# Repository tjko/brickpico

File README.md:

# Brickpico: Smart PWM LED Controller

Bricpico is a smart PWM LED controller based around [Raspberry Pi Pico](https://www.raspberrypi.com/documentation/microcontrollers/raspberry-pi-pico.html) (RP2040 MCU).
Brickpico is mainly meant to controlling various LED lights on LEGO models, but can be used to control any LED lights (or other small loads).

Brickpico operates as standalone controller that incorporates programmable timer to turn lights on/off on a schedule.
BrickPico is an Open-source hardware (OSHW) project.

## Features
* Controls up to 8 to 16 separete channels (LED group)
* Adjustable output brightness (via PWM)
* Adjustable output voltage 5V or 3.3V
* Up to 200mA current output per port (each port has resettable fuse).
* Programmable PWM frequency from 10 to 100000 Hz
* Configurable Lightness/Gamma correction
* Support for configurable lighting "effects" on each channel
* Connectors for common Lego light kits (Light My Bricks, etc.) as well as 2.54mm pin header.
* I2C OLED display module support (128x64 or 128x128)
* I2C Enviromental sensor support (up to 8 sensors)
* Configuration stored on the device itself (in the flash memory).
* SCPI "like" programming interface (see [Command Reference](commands.md))
* WiFi support if opting to mount Pico W on the board.
* HTTP server for monitoring.
* MQTT support for sending status and to receive commands.
* Home Assistant (MQTT Discovery) support
* Telnet server for remote configuration and monitoring.
* SSH server for remote configuration and monitoring.

### Interfaces

* Serial "Console". Primary method for configuring/monitoring FanPico units is via (USB) Serial console (some units also have 3.3V TTL Serial connection).
* Telnet server allows configuration and monitoring over network.
* Web Interface (available when using _Pico W_) over WiFi

For more documentation check [BrickPico Wiki](https://github.com/tjko/brickpico/wiki)

## Where can I get one?
Initially BrickPico is only available as a DIY kit. For places to buy kits, check discussions: [Where to Buy BrickPico](https://github.com/tjko/brickpico/discussions/5)

(Instructions for building the kit can be found at: [BrickPico Wiki](https://github.com/tjko/brickpico/wiki)

### DIY Option
You can upload the Kerber files (found under boards directory) to your favorite PCB maker website and get your boards produced in matter of days.
Component list (BOM or bill of materials) is found under boards directory as well along with the electrical schematics.

### Review Units
If you are member of press (or YouTuber) and would like to review/test Brickpico. Please contact me via email.

## How Can I help?
* Build your own BrickPico and provide feedback, suggestions (see discussion forums).
* If you're into electronics new/improved board designs are most welcome.
* If you're into programming:
  - Create cool (desktop) program that allows easily configuring/controlling BrickPico boards.
  - Help improve the firmware.
* If you're into graphics (or web) design:
  - Help create cool (but lightweight) web interface
  - Create better logo for BrickPico
* As this is Open (Source) Hardware Project, if you like to build (and sell) assembled boards or DIY kits, you'd be most welcome...
* You can always donate (and get your name added to the Sponsors section, if you so wish).

## Hardware
BrickPico is Open Source Hardware, reference design is provided for the "08" model (8 outputs) and "16" model (16 outputs).

Additional models with different combinations of fan outputs could be easily designed (takining into account limitations of Raspberry Pi Pico I/O limits). New and improved PCB models/designs are most welcome.

BrickPico is loosely based on FanPico:
* [FanPico](https://github.com/tjko/fanpico/) - Open Source Smart PWM (PC) Fan Controller.

### Models (PCB designs)
Currently following models are available:

|Model|Outputs|Notes|
|-----|-------|-----|
|[BRICKPICO-08](boards/brickpico-8/)|8||
|[BRICKPICO-16](boards/brickpico-16/)|16|PCB under development|

## Firmware
Firmware is developed in C using the Pico SDK. Pre-compiled firmware is released when there is new major features or bug fixes.

Latest pre-compiled firmware image can be found here: [Releases](https://github.com/tjko/brickpico/releases)

To get latest firmware with latest updates/fixes you must compile the firmware from the sources.

### Installing firmware image
Firmware can be installed via the built-in UF2 bootloader on the Raspberry Pi Pico or using the debug header with Picoprobe, etc...

#### Selecting Right Firmware to use
Each release (zip file) contains multiple different firmware files.
Make sure to select firmware for the board you're using and for the pico model ("pico_w" if using Pico W).

Firmware file names have format: brickpico-<board_model>-<pico_model>.uf2
```
brickpico-08-pico.uf2
brickpico-08-pico_w.uf2
brickpico-16-pico.uf2
brickpico-16-pico_w.uf2
```

#### Upgrading Firmware
Firmware upgrade steps:
* Boot Pico into UF2 bootloader. This can be done in two ways:
  1)  Press and hold "bootsel" button and then press and release "reset" button.
  2)  Issue command: SYS:UPGRADE
* Copy firmware file to the USB mass storage device that appears.
* As soon as firmware copy is complete, Pico will reboot and run the fanpico firmware.

### Building Firmware Images

Raspberry Pi Pico C/C++ SDK is required for compiling the firmware:

#### Requirements / Dependencies
* [Raspberry Pi Pico C/C++ SDK](https://www.raspberrypi.com/documentation/microcontrollers/c_sdk.html)
* [cJSON](https://github.com/DaveGamble/cJSON)
* [pico-lfs](https://github.com/tjko/pico-lfs)
* [ss_oled-lib](https://github.com/tjko/ss_oled-lib)
* [libb64](https://github.com/libb64/libb64)
* [pico-telnetd](https://github.com/tjko/pico-telnetd)

##### Install Pico SDK
Pico SDK must be installed working before you can compile fanpico.

Instructions on installing Pico SDK see: [Getting started with Raspberry Pi Pico](https://datasheets.raspberrypi.com/pico/getting-started-with-pico.pdf)

(Make sure PICO_SDK_PATH environment variable is set)

##### Downloading sources

Create some directory for building fanpico ('src' used in this example):
```
$ mkdir src
$ cd src
$ git clone https://github.com/tjko/brickpico.git
$ git submodule update --init --recursive
```

##### Building fanpico firmware

To build brickpico firmware, first create a build directory:
```
$ cd brickpico
$ mkdir build
```

Select which board to build firmware for (default is "08") and which Pico is to be used (default is "pico_w"):
```
$ cd build
$ cmake -DBRICKPICO_BOARD=16 -DPICO_BOARD=pico_w ..
```

Then compile fanpico:
```
$ make -j
```

After successful compile you should see firmware binary in the build directory:
subdirectory:

```
$ ls *.uf2
brickpico.uf2
```

If you have picotool installed you can check the firmware image information:
```
$ picotool info -a brickpico.uf2
File brickpico.uf2 family ID 'rp2040':

Program Information
 name:              brickpico
 version:           1.4.0beta
 web site:          https://github.com/tjko/brickpico/
 description:       BrickPico-08 - Smart LED Controller
 features:          USB stdin / stdout
 boot settings:     bootdelay = 0
                    safemode = 0
 binary start:      0x10000000
 binary end:        0x1010b638
 embedded drive:    0x101c0000-0x10200000 (256K): littlefs

Fixed Pin Information
 0:                 TX (Serial)
 1:                 RX (Serial)
 2:                 SCK (SPI)
 3:                 MOSI (SPI)
 4:                 MISO (SPI)
 5:                 CS (SPI)
 6:                 PWM7 signal (output)
 7:                 PWM8 signal (output)
 16:                PWM1 signal (output)
 17:                PWM2 signal (output)
 18:                PWM3 signal (output)
 19:                PWM4 signal (output)
 20:                PWM5 signal (output)
 21:                PWM6 signal (output)
 22:                LCD DC (SPI)
 26:                SDA (I2C)
 27:                SCL (I2C)
 28:                LCD Reset (SPI)

Build Information
 sdk version:       2.1.1
 pico_board:        pico_w
 boot2_name:        boot2_w25q080
 build date:        Jul 14 2025
 build attributes:  Release

Metadata Blocks
 none
```

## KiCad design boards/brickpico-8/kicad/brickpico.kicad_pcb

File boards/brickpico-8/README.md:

# BRICKPICO-08 PCB

PCB Size: 86mm x 79.5mm

## Change Log

v1.0 
- First Prototye

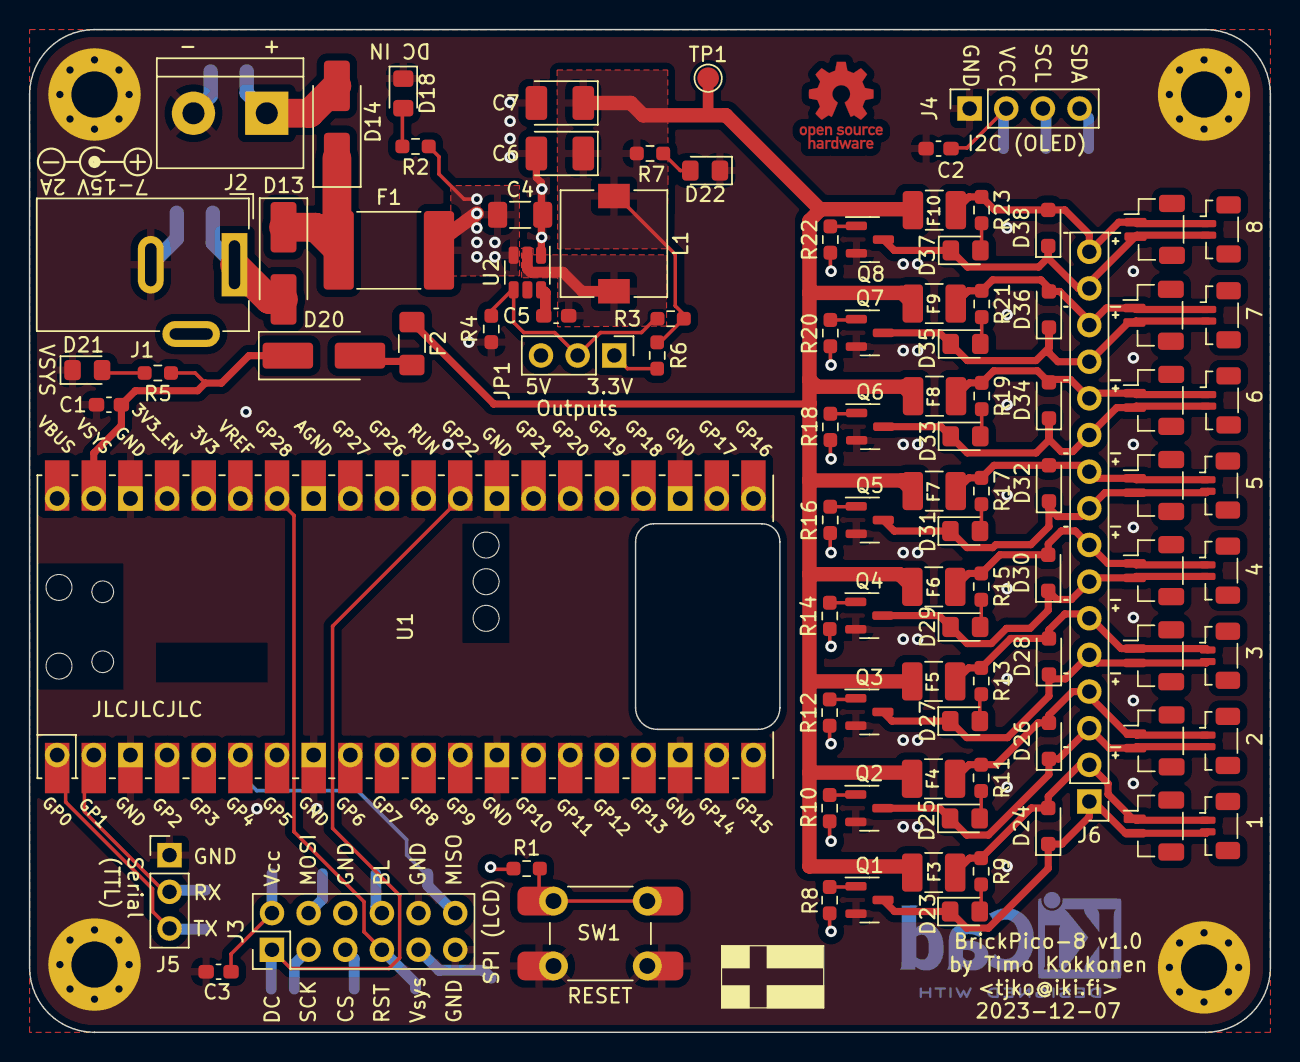
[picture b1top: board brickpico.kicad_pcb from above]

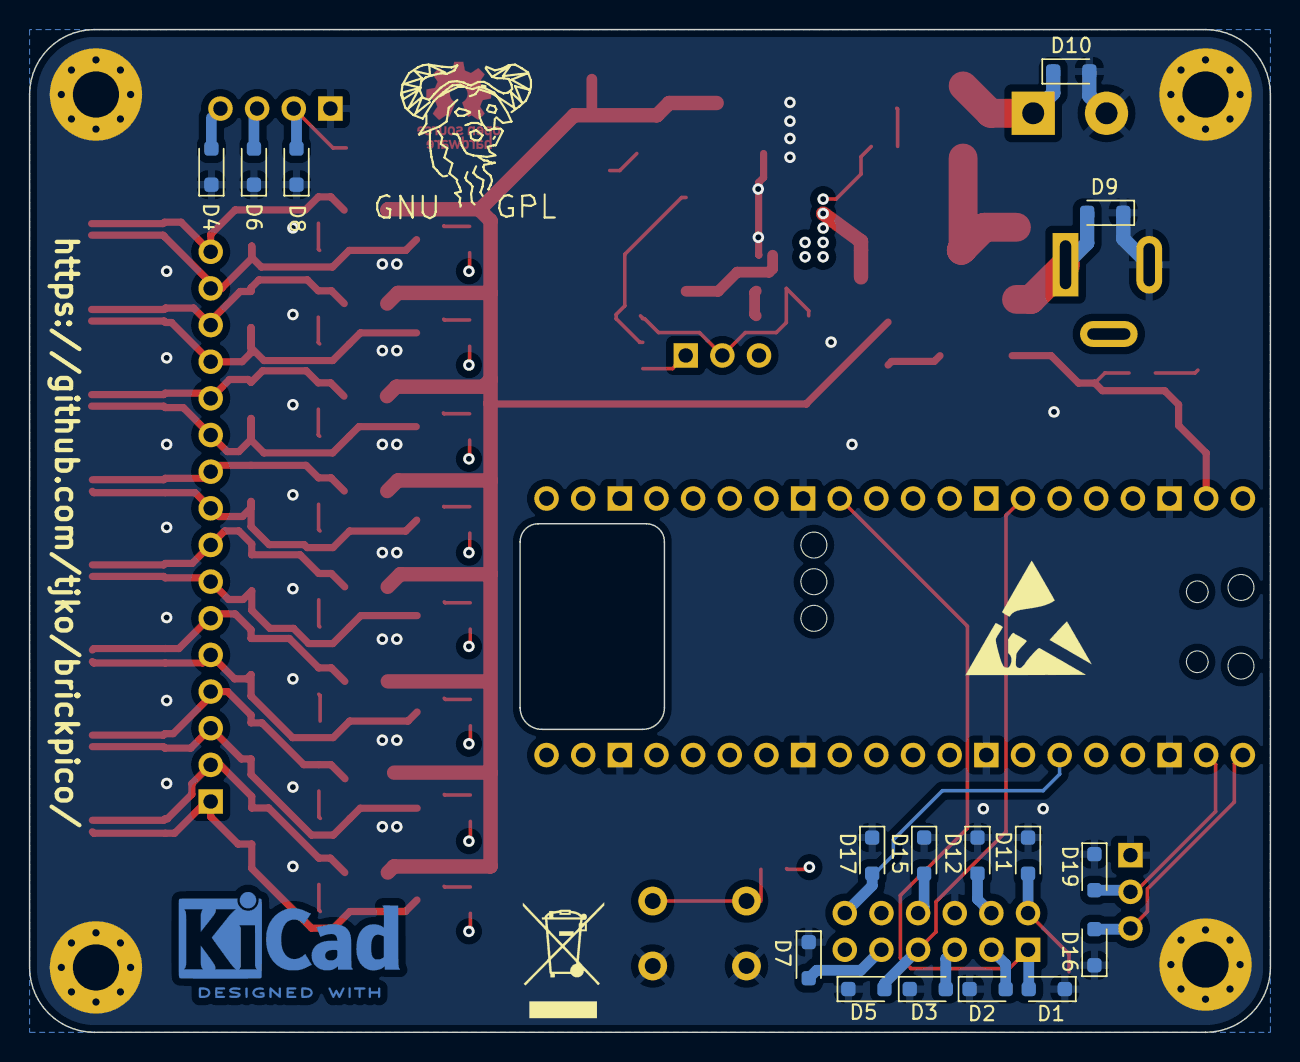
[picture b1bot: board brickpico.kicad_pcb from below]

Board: 4 copper layers, 86.0 x 69.5 mm, 118 parts (16 on the bottom side), 68 nets.

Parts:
C1, C2, C3, C5: 0.1uF; C_0603_1608Metric_Pad1.08x0.95mm_HandSolder
C4: 10uF 50V; C_1206_3216Metric_Pad1.33x1.80mm_HandSolder
C6, C7: 22uF 16V; CP_EIA-3528-21_Kemet-B_Pad1.50x2.35mm_HandSolder
D1, D2, D3, D4, D5, D6, D8, D11, D12, D15, D16, D17, D19: 3.3V; D_SOD-323_HandSoldering
D7, D24, D26, D28, D30, D32, D34, D36, D38: 5V; D_SOD-323_HandSoldering
D9, D10: 12V; D_SOD-323_HandSoldering
D13, D14: SK54A-LTP; D_SMA_Handsoldering
D18, D21, D22, D23, D25, D27, D29, D31, D33, D35, D37: LED; LED_0805_2012Metric_Pad1.15x1.40mm_HandSolder
D20: SM5819PL 1A; D_SMA_Handsoldering
F1: Polyfuse 3A; Fuse_2920_7451Metric_Pad2.10x5.45mm_HandSolder
F2: Polyfuse 500mA; Fuse_1206_3216Metric_Pad1.42x1.75mm_HandSolder
F3, F4, F5, F6, F7, F8, F9, F10: Polyfuse 200mA; Fuse_1210_3225Metric_Pad1.42x2.65mm_HandSolder
H1, H2, H3, H4: MountingHole_Pad; MountingHole_3.2mm_M3_Pad_Via
J1: DC Connector; BarrelJack_Wuerth_6941xx301002
J2: Terminal Block; TerminalBlock_bornier-2_P5.08mm
J3: SPI (LCD); PinHeader_2x06_P2.54mm_Vertical
J4: I2C (OLED); PinSocket_1x04_P2.54mm_Vertical
J5: Serial (TTL); PinHeader_1x03_P2.54mm_Vertical
J6: Conn_01x16; PinHeader_1x16_P2.54mm_Vertical
J7, J8, J9, J10, J11, J12, J13, J14: JST SUR; JST_SUR_BM02B-SURS-TF_1x02-1MP_P0.80mm_Vertical
J15, J16, J17, J18, J19, J20, J21, J22: JST SRS; JST_SH_BM02B-SRSS-TB_1x02-1MP_P1.00mm_Vertical
JP1: Conn_01x03; PinHeader_1x03_P2.54mm_Vertical
L1: 3.3uH; L_7.3x7.3_H3.5_HandSolder
Q1, Q2, Q3, Q4, Q5, Q6, Q7, Q8: 2N7002K; SOT-23
R1, R8, R10, R12, R14, R16, R18, R20, R22: 1K; R_0603_1608Metric_Pad0.98x0.95mm_HandSolder
R2: 49.9K; R_0603_1608Metric_Pad0.98x0.95mm_HandSolder
R3: 56.2K; R_0603_1608Metric_Pad0.98x0.95mm_HandSolder
R4, R5, R7, R9, R11, R13, R15, R17, R19, R21, R23: 10K; R_0603_1608Metric_Pad0.98x0.95mm_HandSolder
R6: 82K; R_0603_1608Metric_Pad0.98x0.95mm_HandSolder
SW1: Reset; SW_PUSH_6mm_SMD_2
TP1: TestPoint; TestPoint_Pad_D1.5mm
U1: Pico; RPi_Pico_PicoW_SMD_TH
U2: AP62300TWU; TSOT-26

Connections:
3V3: C2.2, C3.1, D8.2 (A2), D11.2 (A2), D15.2 (A2), J3.2, J3.8, J4.2, U1.36 (3V3)
/LED Connectors/Output 1/OUT_N: D23.1 (K), D24.1 (A1), J6.1, J7.2, J15.2, Q1.3 (D)
/LED Connectors/Output 1/OUT_P: D24.2 (A2), F3.2, J6.2, J7.1, J15.1, R9.1
/LED Connectors/Output 2/OUT_N: D25.1 (K), D26.1 (A1), J6.3, J8.2, J16.2, Q2.3 (D)
/LED Connectors/Output 2/OUT_P: D26.2 (A2), F4.2, J6.4, J8.1, J16.1, R11.1
/LED Connectors/Output 3/OUT_N: D27.1 (K), D28.1 (A1), J6.5, J9.2, J17.2, Q3.3 (D)
/LED Connectors/Output 3/OUT_P: D28.2 (A2), F5.2, J6.6, J9.1, J17.1, R13.1
/LED Connectors/Output 4/OUT_N: D29.1 (K), D30.1 (A1), J6.7, J10.2, J18.2, Q4.3 (D)
/LED Connectors/Output 4/OUT_P: D30.2 (A2), F6.2, J6.8, J10.1, J18.1, R15.1
/LED Connectors/Output 5/OUT_N: D31.1 (K), D32.1 (A1), J6.9, J11.2, J19.2, Q5.3 (D)
/LED Connectors/Output 5/OUT_P: D32.2 (A2), F7.2, J6.10, J11.1, J19.1, R17.1
/LED Connectors/Output 6/OUT_N: D33.1 (K), D34.1 (A1), J6.11, J12.2, J20.2, Q6.3 (D)
/LED Connectors/Output 6/OUT_P: D34.2 (A2), F8.2, J6.12, J12.1, J20.1, R19.1
/LED Connectors/Output 7/OUT_N: D35.1 (K), D36.1 (A1), J6.13, J13.2, J21.2, Q7.3 (D)
/LED Connectors/Output 7/OUT_P: D36.2 (A2), F9.2, J6.14, J13.1, J21.1, R21.1
/LED Connectors/Output 8/OUT_N: D37.1 (K), D38.1 (A1), J6.15, J14.2, J22.2, Q8.3 (D)
/LED Connectors/Output 8/OUT_P: D38.2 (A2), F10.2, J6.16, J14.1, J22.1, R23.1
CS: D3.2 (A2), J3.5, U1.7 (GPIO5)
DC: D1.2 (A2), J3.1, U1.29 (GPIO22)
DC_IN: C4.2, F1.2, R2.1, U2.3 (IN)
GND: C1.2, C2.1, C3.2, C4.1, C6.2, C7.2, D1.1 (A1), D2.1 (A1), D3.1 (A1), D4.1 (A1), D5.1 (A1), D6.1 (A1), D7.1 (A1), D8.1 (A1), D9.1 (A1), D10.2 (A2), D11.1 (A1), D12.1 (A1), D15.1 (A1), D16.1 (A1), D17.1 (A1), D18.1 (K), D19.1 (A1), D21.1 (K), D22.1 (K), H1.1, H2.1, H3.1, H4.1, J1.2, J2.2, J3.6, J3.10, J3.11, J4.1, J5.1, Q1.2 (S), Q2.2 (S), Q3.2 (S), Q4.2 (S), Q5.2 (S), Q6.2 (S), Q7.2 (S), Q8.2 (S), R4.1, SW1.2, U1.3 (GND), U1.8 (GND), U1.13 (GND), U1.18 (GND), U1.23 (GND), U1.28 (GND), U1.38 (GND), U2.1 (GND)
LED_PWR_1: C6.1, C7.1, F2.1, F3.1, F4.1, F5.1, F6.1, F7.1, F8.1, F9.1, F10.1, L1.2, R3.2, R6.2, R7.1, TP1.1
MISO: D17.2 (A2), J3.12, U1.6 (GPIO4)
MOSI: D12.2 (A2), J3.4, U1.5 (GPIO3)
unnamed: D10.1 (A1), D14.2 (A), J2.1
unnamed: D9.2 (A2), D13.2 (A), J1.1
unnamed: D13.1 (K), D14.1 (K), F1.1
unnamed: D18.2 (A), R2.2
unnamed: D20.2 (A), F2.2
unnamed: D21.2 (A), R5.2
unnamed: D22.2 (A), R7.2
unnamed: D23.2 (A), R9.2
unnamed: D25.2 (A), R11.2
unnamed: D27.2 (A), R13.2
unnamed: D29.2 (A), R15.2
unnamed: D31.2 (A), R17.2
unnamed: D33.2 (A), R19.2
unnamed: D35.2 (A), R21.2
unnamed: D37.2 (A), R23.2
unnamed: JP1.1 (A), R6.1
unnamed: JP1.2 (C), R3.1, R4.2, U2.4 (FB)
unnamed: Q1.1 (G), R8.1
unnamed: Q2.1 (G), R10.1
unnamed: Q3.1 (G), R12.1
unnamed: Q4.1 (G), R14.1
unnamed: Q5.1 (G), R16.1
unnamed: Q6.1 (G), R18.1
unnamed: Q7.1 (G), R20.1
unnamed: Q8.1 (G), R22.1
unnamed: R1.2, SW1.1
unnamed: R1.1, U1.30 (RUN)
unnamed: C5.1, U2.6 (BST)
unnamed: C5.2, L1.1, U2.2 (SW)
PWM0A: R8.2, U1.21 (GPIO16)
PWM0B: R10.2, U1.22 (GPIO17)
PWM1A: R12.2, U1.24 (GPIO18)
PWM1B: R14.2, U1.25 (GPIO19)
PWM2A: R16.2, U1.26 (GPIO20)
PWM2B: R18.2, U1.27 (GPIO21)
PWM3A: R20.2, U1.9 (GPIO6)
PWM3B: R22.2, U1.10 (GPIO7)
RST: D5.2 (A2), J3.7, U1.34 (GPIO28_ADC2)
RX: D19.2 (A2), J5.2, U1.2 (GPIO1)
SCK: D2.2 (A2), J3.3, U1.4 (GPIO2)
SCL: D6.2 (A2), J4.3, U1.32 (GPIO27_ADC1)
SDA: D4.2 (A2), J4.4, U1.31 (GPIO26_ADC0)
TX: D16.2 (A2), J5.3, U1.1 (GPIO0)
VSYS: C1.1, D7.2 (A2), D20.1 (K), J3.9, R5.1, U1.39 (VSYS)

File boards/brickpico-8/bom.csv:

"Item","Qty","Reference(s)","Value","LibPart","Footprint","Datasheet","DNP","LCSC Part Number","Mouser Part Number"
"1","4","C1, C2, C3, C5","0.1uF","Device:C","Capacitor_SMD:C_0603_1608Metric_Pad1.08x0.95mm_HandSolder","~","","C1591","80-C0603C104Z3VAC"
"2","1","C4","10uF 50V","Device:C","Capacitor_SMD:C_1206_3216Metric_Pad1.33x1.80mm_HandSolder","~","","C89632",""
"3","2","C6, C7","22uF 25V","Device:C_Polarized","Capacitor_Tantalum_SMD:CP_EIA-3528-21_Kemet-B_Pad1.50x2.35mm_HandSolder","~","","C12891",""
"4","13","D1, D2, D3, D4, D5, D6, D8, D11, D12, D15, D16, D17, D19","3.3V","Device:D_TVS","Diode_SMD:D_SOD-323_HandSoldering","~","","C78439","750-CPDV3V3A-HF"
"5","9","D7, D24, D26, D28, D30, D32, D34, D36, D38","5V","Device:D_TVS","Diode_SMD:D_SOD-323_HandSoldering","~","","C5180216","621-DESD5V0U1BA-7"
"6","2","D9, D10","15V","Device:D_TVS","Diode_SMD:D_SOD-323_HandSoldering","~","","C5199169",""
"7","2","D13, D14","SK54A-LTP","Device:D_Schottky","Diode_SMD:D_SMA_Handsoldering","~","","C669016","833-SK54A-LTP"
"8","11","D18, D21, D22, D23, D25, D27, D29, D31, D33, D35, D37","LED","Device:LED","LED_SMD:LED_0805_2012Metric_Pad1.15x1.40mm_HandSolder","~","","C434432","710-150080GS75000"
"9","1","D20","SM5819PL 1A","Device:D_Schottky","Diode_SMD:D_SMA_Handsoldering","~","","C669023","833-SM5819PL-TP"
"10","1","F1","Polyfuse 2A","Device:Polyfuse_Small","Fuse:Fuse_2920_7451Metric_Pad2.10x5.45mm_HandSolder","~","","C910843",""
"11","1","F2","Polyfuse 350mA","Device:Polyfuse_Small","Fuse:Fuse_1206_3216Metric_Pad1.42x1.75mm_HandSolder","~","","C70072",""
"12","8","F3, F4, F5, F6, F7, F8, F9, F10","Polyfuse 200mA","Device:Polyfuse_Small","Fuse:Fuse_1210_3225Metric_Pad1.42x2.65mm_HandSolder","~","","C70088","530-0ZCJ0020FF2E"
"13","4","H1, H2, H3, H4","MountingHole_Pad","Mechanical:MountingHole_Pad","MountingHole:MountingHole_3.2mm_M3_Pad_Via","~","","N/A","N/A"
"14","1","J1","DC Connector","Connector:Barrel_Jack_Switch","Connector_BarrelJack:BarrelJack_Wuerth_6941xx301002","~","","C720558",""
"15","1","J2","Terminal Block","Connector_Generic:Conn_01x02","TerminalBlock:TerminalBlock_bornier-2_P5.08mm","~","","C1509679",""
"16","1","J3","SPI (LCD)","Connector_Generic:Conn_02x06_Odd_Even","Connector_PinHeader_2.54mm:PinHeader_2x06_P2.54mm_Vertical","~","","C492423",""
"17","1","J4","I2C (OLED)","Connector_Generic:Conn_01x04","Connector_PinSocket_2.54mm:PinSocket_1x04_P2.54mm_Vertical","~","","C2691448",""
"18","1","J5","Serial (TTL)","Connector_Generic:Conn_01x03","Connector_PinHeader_2.54mm:PinHeader_1x03_P2.54mm_Vertical","~","","C124376",""
"19","1","J6","Conn_01x16","Connector_Generic:Conn_01x16","Connector_PinHeader_2.54mm:PinHeader_1x16_P2.54mm_Vertical","~","","C2894939",""
"20","8","J7, J8, J9, J10, J11, J12, J13, J14","JST SUR","Connector_Generic:Conn_01x02","Connector_JST:JST_SUR_BM02B-SURS-TF_1x02-1MP_P0.80mm_Vertical","~","","C385130",""
"21","8","J15, J16, J17, J18, J19, J20, J21, J22","JST SRS","Connector_Generic:Conn_01x02","Connector_JST:JST_SH_BM02B-SRSS-TB_1x02-1MP_P1.00mm_Vertical","~","","C160388",""
"22","1","JP1","Conn_01x03","Jumper:Jumper_3_Bridged12","Connector_PinHeader_2.54mm:PinHeader_1x03_P2.54mm_Vertical","~","","C124376",""
"23","1","L1","3.3uH","Device:L","FanPico:L_7.3x7.3_H3.5_HandSolder","~","","C5189747",""
"24","8","Q1, Q2, Q3, Q4, Q5, Q6, Q7, Q8","2N7002K","Transistor_FET:2N7002K","Package_TO_SOT_SMD:SOT-23","https://www.diodes.com/assets/Datasheets/ds30896.pdf","","C414015","512-2N7002K"
"25","9","R1, R8, R10, R12, R14, R16, R18, R20, R22","1K","Device:R","Resistor_SMD:R_0603_1608Metric_Pad0.98x0.95mm_HandSolder","~","","C22548",""
"26","1","R2","49.9K","Device:R","Resistor_SMD:R_0603_1608Metric_Pad0.98x0.95mm_HandSolder","~","","C114624",""
"27","1","R3","52.3K","Device:R","Resistor_SMD:R_0603_1608Metric_Pad0.98x0.95mm_HandSolder","~","","C185323",""
"28","11","R4, R5, R7, R9, R11, R13, R15, R17, R19, R21, R23","10K","Device:R","Resistor_SMD:R_0603_1608Metric_Pad0.98x0.95mm_HandSolder","~","","C98220",""
"29","1","R6","80K","Device:R","Resistor_SMD:R_0603_1608Metric_Pad0.98x0.95mm_HandSolder","~","","C3014409",""
"30","1","SW1","Reset","Switch:SW_Push","FanPico:SW_PUSH_6mm_SMD_2","~","","C221880",""
"31","1","TP1","TestPoint","Connector:TestPoint","TestPoint:TestPoint_Pad_D1.5mm","~","","N/A","N/A"
"32","1","U1","Pico","fanpico:Pico","FanPico:RPi_Pico_PicoW_SMD_TH","","","","358-SC0918"
"33","1","U2","AP62301WU","Regulator_Switching:AP62300TWU","FanPico:TSOT-26","https://www.diodes.com/assets/Datasheets/AP62300_AP62301_AP6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","","C3194340","621-AP62301WU-7"

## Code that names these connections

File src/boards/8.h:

/* boards/8.h */


#define BRICKPICO_MODEL     "08"

#define OUTPUT_COUNT     8   /* Number of PWM outputs on the board */

#ifdef LIB_PICO_CYW43_ARCH
#define LED_PIN -1
#else
#define LED_PIN 25
#endif


/* Pins for PWM outputs. */

#define PWM1_PIN       16  /* PWM0A */
#define PWM2_PIN       17  /* PWM0B */
#define PWM3_PIN       18  /* PWM1A */
#define PWM4_PIN       19  /* PWM1B */
#define PWM5_PIN       20  /* PWM2A */
#define PWM6_PIN       21  /* PWM2B */
#define PWM7_PIN        6  /* PWM3A */
#define PWM8_PIN        7  /* PWM3B */
#define PWM9_PIN       -1  /* PWM4A */
#define PWM10_PIN      -1  /* PWM4B */
#define PWM11_PIN      -1  /* PWM5A */
#define PWM12_PIN      -1  /* PWM5B */
#define PWM13_PIN      -1  /* PWM6A */
#define PWM14_PIN      -1  /* PWM6B */
#define PWM15_PIN      -1  /* PWM7A */
#define PWM16_PIN      -1  /* PWM7B */


/* Interface Pins */

/* I2C */
#define I2C_HW          2  /* 1=i2c0, 2=i2c1, 0=bitbang... */
#define SDA_PIN        26
#define SCL_PIN        27

/* Serial */
#define TX_PIN          0
#define RX_PIN          1

/* SPI */
#define SCK_PIN         2
#define MOSI_PIN        3
#define MISO_PIN        4
#define CS_PIN          5

#define DC_PIN         22
#define LCD_RESET_PIN  28
#define LCD_LIGHT_PIN  -1


#define OLED_DISPLAY 1
#define LCD_DISPLAY 0

#define TTL_SERIAL   1
#define TTL_SERIAL_UART uart0
#define TTL_SERIAL_SPEED 115200

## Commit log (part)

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2023-12-01 Add submodules.
2023-12-01 Remove LCD module
2023-12-01 Initial fw build working.
2023-12-01 more stuff from fanpico
2023-12-02 more basic functionality added
2023-12-02 Temp pwm setting.
2023-12-03 Initial commands document.
2023-12-03 Initial readme added.
2023-12-03 Add SYS:PWMfreq documentation.
2023-12-03 more tweaks
2023-12-04 Web UI initiallyh working.
2023-12-05 more UI experiments
2023-12-09 Support for different board models.
2023-12-09 OLED working on both 128x128 and 128x64 resolutions.
2023-12-09 Add SYS:TIMEZONE command for manually specifying timezone.
2023-12-09 Move timezone setup.
2023-12-10 Web UI: basic functionality working.
2023-12-10 Initial timer stuff.
2023-12-11 Timer events can now be configured.
2023-12-11 Add CONF:TIMERS:DEL command.
2023-12-12 Timer events working.
2023-12-13 Update WRITE commands.
2023-12-13 Add github workflows from fanpico.
2023-12-13 Initial firmware image fully functional. (#1)
    Initial firmware heavily based on FanPico (https://github.com/tjko/fanpico/) functional on prototype board.
2023-12-13 Fix brickpico-8 build.
2023-12-13 Fix brickpico-8 build again.
2023-12-14 Web interface scaling "fixed".
2023-12-14 Add brickpico-08 board.
2023-12-15 Add new commands: CONF:DEFAULT:PWM CONF:DEFAULT:STATE
2023-12-15 Update CSV and JSON outputs to use ON/OFF as status instead of 1/0.
2023-12-15 Update web layout
2023-12-15 Add initial web interace screenshots.
2023-12-15 Update default board.
2023-12-17 Initial MQTT client working.
2023-12-17 DNS lookups working in MQTT client.
2023-12-17 More updates to MQTT.
2023-12-18 Initial commands from MQTT working.
2023-12-18 Add PCB image.
2023-12-18 Add MQTT support. (#2)
2023-12-19 Updated photo of brickpico-08.
2023-12-19 Update brightness slider color.
2023-12-19 Update web UI images.
2023-12-19 Add bill of materials for brickpico-8.
2023-12-19 Fix board name.
2023-12-19 Fix wront type argument to printf.
2023-12-19 Add MQTT command documentation.
2023-12-19 Fix broken links in index.
2023-12-20 Fix firmware upgrade screen text.
2023-12-20 Add extra entropy to mbedtls during build time.
2023-12-20 Cleanup logging.
2023-12-20 Cleanup formatting.
2023-12-21 Add status page to web interface.
2023-12-21 Add OLED screen layout examples.
2023-12-22 MQTT: Initial support for response topic to respond to commands received.
2023-12-23 Support for SCPI commands via MQTT.
2023-12-23 Add SYStem:MQTT:RESPonse command.
2023-12-23 Enhanced MQTT support. (#6)
    Support for receiving SCPI command via MQTT. And sending responses to command via a response topic.
    New commands:
    SYStem:MQTT:SCPI
    SYStem:MQTT:SCPI?
    SYStem:MQTT:RESPonse
    SYStem:MQTT:RESPonse?
2023-12-23 Fix timer event weekday check.
2023-12-31 Change command data structures to 'const' so they get stored in flash memory.
2023-12-31 Switch more commands to use generic helper functions.
2024-01-01 More cleanup of command implementations.
2024-01-02 MQTT: support for sending per output status as well as unit temperature.
2024-01-03 Updated reconnect logic.
2024-01-04 Update documentation and add support subscribing error/warning topics from broker.
2024-01-04 Fix compile on pico boards.
2024-01-04 Update to MQTT client. (#7)
    - Support for sending per output status as well as unit temperature.
    - Updated reconnect logic.
    - Update documentation and add support subscribing error/warning topics…
2024-01-05 Add Millennium Falcon PNG
2024-01-05 More images
2024-01-05 Update README and some images. (#8)
2024-01-06 Testing saving RTC clock time in RAM for soft reboots.
2024-01-06 Initial implementation of storing log messages in RAM ringbuffer.
2024-01-07 Enable HTTPS support.
2024-01-07 Enable HTTPS support and persistent memory to keep logs and RTC time after soft reset. (#9)
2024-01-07 Updated UCS Millennium Falcon png.
2024-01-08 Support for using multi-part (EC) private keys.
    Use "SYS:TLS:PKEY 2" to upload/paste EC private key and parameters
    (when there is two PEM sections/documents).
2024-01-08 Enable MbedTLS debug ouput in Debug builds.
2024-01-13 Add PCB diagram.
2024-01-13 Updated diagram.
2024-01-13 Fix lines
2024-01-18 MQTT updates and nes SYS:FLASH? command.
2024-01-18 Fix link for SYS:FLASH?
2024-01-18 Minor MQTT update and add new command SYS:FLASH? (#10)
2024-01-25 cleanup utility functions
2024-01-26 Update ringbuffer routines.
2024-01-27 Initial TCP/Telnet server working with stdio.
2024-01-28 more telnet functionality
2024-01-28 Telnet authentication working.
2024-01-29 last version
2024-01-29 move telnet server into separate lib
2024-01-30 Add telnet configuration commands.
2024-01-31 Telnet server now using pico-telnetd library as submodule.
2024-01-31 Add Telnet (server) support. (#11)
    - Add support for telnet (and "raw TCP") server using pico-telnetd library.
2024-02-01 Fix saving of SYS:TELNET:AUTH setting.
2024-02-01 Update credits.
2024-02-01 New command SYS:LFS?
2024-02-01 Add SYS:LFS? documentation.
2024-02-21 Fix SYS:TELNET:AUTH and add SYS:LFS? command. (#12)
2024-02-21 Switch to using pico-lfs library for littlefs.
2024-02-21 Fix hostname validation.
2024-02-21 Switch to using pico-lfs library for littlefs. (#13)
2024-02-25 Cleanup compiler warnings.
2024-03-14 Add new command SYS:LFS:FORMAT
2024-03-14 Fix possible hang if LFS needed to be initialized during boot.
2024-03-14 Fix possible hang when initializing LFS. (#15)
    * Add new command SYS:LFS:FORMAT
    * Fix possible hang if LFS needed to be initialized during boot.
2024-07-28 Update workflow to use v4 actions.
2024-07-28 fix syntax
2024-07-28 Update workflow to use v4 actions. (#18)
2024-08-14 Fix memory leak when opening MQTT connections.
2024-12-23 Fixed compile issues on Pico-SDK 2.1.0
2024-12-23 Update pico_telnetd and ss_oled-lib libraries.
2024-12-23 Fix compiling for pico2 and pico2_w.
2024-12-23 update compile workflow to use new sdk
2024-12-23 Update codeql to use new SDK.
2024-12-23 Add BRICKPICO_BUILD_TAG setting.
2024-12-23 Include license files in firmware zip files.
2024-12-23 Pico-SDK v2.1.0 support (#21)
    * Fixed compile issues on Pico-SDK 2.1.0
    * Update pico_telnetd and ss_oled-lib libraries.
    * Fix compiling for pico2 and pico2_w.
    * Include license files in firmware zip files.
2024-12-24 Add new commands to set WiFi authentication mode: - SYS:WIFI:AUTHmode - SYS:WIFI:AUTHmode?
2024-12-24 WiFi updates (#22)
    - Add new commands to set WiFi authentication mode:
    - SYS:WIFI:AUTHmode
    - SYS:WIFI:AUTHmode?
    - Fix possible hang if WiFi fails to connect.
2024-12-30 Initial HomeAssistant MQTT Discovery support.
2024-12-31 Home Assistant integration working.
2024-12-31 Fix compiling for pico.
2024-12-31 Home Assistant (MQTT Discovery) Support (#23)
    * Initial HomeAssistant MQTT Discovery support (using Device Discovery)
    * New commands:
    - SYStem:MQTT:HA:DISCovery
    - SYStem:MQTT:HA:DISCovery?
2025-01-03 Initial light effects support added.
2025-01-04 Updates to engine and new pulse effect.
2025-01-04 Add documentation.
2025-01-04 Initial lighting effects support. (#24)
    * Initial light effects support added.
    * New commands:
    - CONF:OUTPUTx:EFFect
    - CONF:OUTPUTx:EFFect?
2025-01-10 Add initial Lightness/Gamma correction support.
2025-01-10 Add new commands: - SYS:GAMMA - SYS:GAMMA?
2025-01-10 fix markdown
2025-01-10 Add initial Lightness/Gamma correction support. (#25)
    * Add initial Lightness/Gamma correction support.
    * New commands:
    - SYS:GAMMA
    - SYS:GAMMA?
2025-01-11 Also build pico2/pico2_w targets.
2025-01-11 Update picotool output.
2025-04-06 Updates to I2C support and add pico-sensor-lib library.
2025-04-08 Initial port of "VSENSOR" stuff from FanPico.
2025-04-22 Initial VSENSOR support working.
2025-04-25 Fix SYS:MEM command on Pico 2 (W).
2025-07-14 Add LFS commands from FanPico.
2025-07-14 Display sensor information on web interface.
2025-07-14 Update manual.
2025-07-14 Add boot settings configurable using picotool.
2025-07-14 fixes
2025-07-14 add i2c.c
2025-07-14 Add I2C sensor support. (#30)
2025-07-15 Add SSH Server.
2025-07-15 Add wolfSSL config.
2025-07-15 Update login banner.
2025-07-15 Add SSH Server. (#31)
2025-07-17 Fix temperature readings on RP2350B.
2025-08-27 Update Pico-SDK and libraries.
2025-08-27 Fix compile error
2025-08-27 Update Pico-SDK and other libraries. (#32)
2025-08-28 Add ACL support to SSH and Telnet servers.
